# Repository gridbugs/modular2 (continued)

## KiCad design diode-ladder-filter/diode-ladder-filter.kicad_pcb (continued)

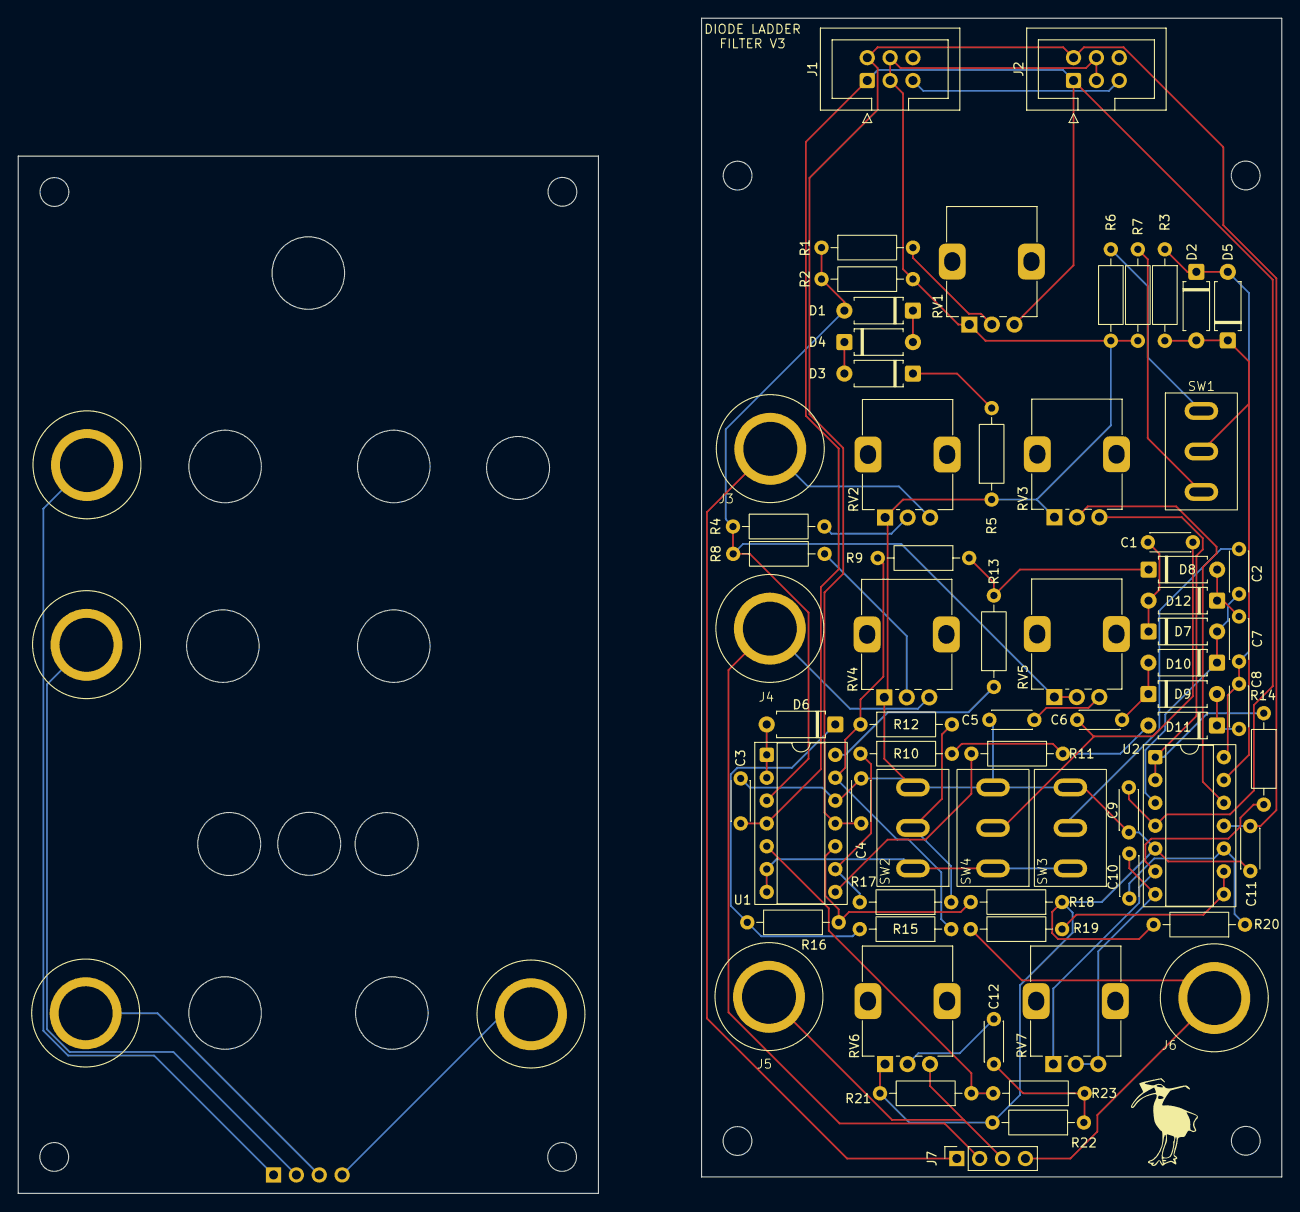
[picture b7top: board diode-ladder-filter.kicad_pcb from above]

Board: 2 copper layers, 64.5 x 128.8 mm, 80 parts (1 on the bottom side), 51 nets.

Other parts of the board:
H1, H2, H3, H4, H5, H6, H7, H8: MountingHole_3.2mm_M3

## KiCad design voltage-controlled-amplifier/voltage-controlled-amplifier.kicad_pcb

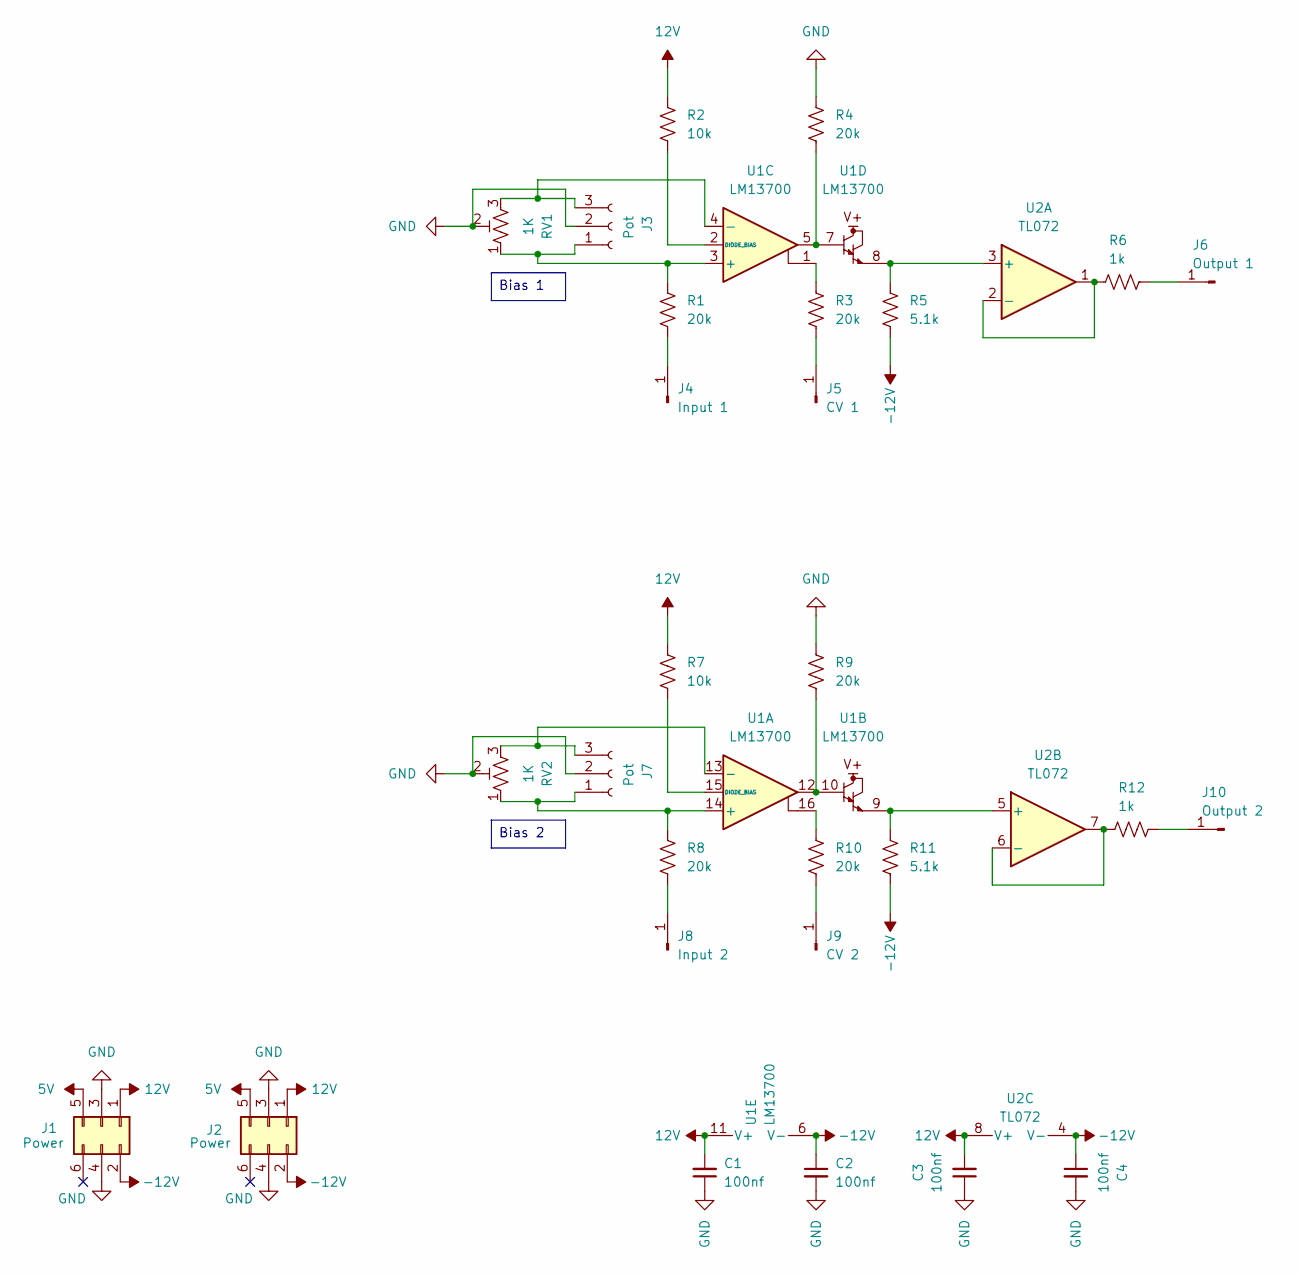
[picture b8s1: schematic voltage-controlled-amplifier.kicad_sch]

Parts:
C1, C2, C3, C4: 100nf; C_Disc_D4.3mm_W1.9mm_P5.00mm
J1, J2: Power; IDC-Header_2x03_P2.54mm_Vertical
J3, J7: Pot; pot
J4: Input 1; banana-jack
J5: CV 1; banana-jack
J6: Output 1; banana-jack
J8: Input 2; banana-jack
J9: CV 2; banana-jack
J10: Output 2; banana-jack
R1, R3, R4, R8, R9, R10: 20k; R_Axial_DIN0207_L6.3mm_D2.5mm_P10.16mm_Horizontal
R2, R7: 10k; R_Axial_DIN0207_L6.3mm_D2.5mm_P10.16mm_Horizontal
R5, R11: 5.1k; R_Axial_DIN0207_L6.3mm_D2.5mm_P10.16mm_Horizontal
R6, R12: 1k; R_Axial_DIN0207_L6.3mm_D2.5mm_P10.16mm_Horizontal
RV1, RV2: 1K; pot-socket
U1: LM13700; DIP-16_W7.62mm_Socket
U2: TL072; DIP-8_W7.62mm_Socket

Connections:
5V: J1.5, J2.5
12V: C1.2, C3.2, J1.1, J2.1, R2.1, R7.1, U1.11 (V+), U2.8 (V+)
-12V: C2.1, C4.1, J1.2, J2.2, R5.2, R11.2, U1.6 (V-), U2.4 (V-)
GND: C1.1, C2.2, C3.1, C4.2, J1.3, J1.4, J2.3, J2.4, J3.2, J7.2, R4.1, R9.1, RV1.2, RV2.2
unnamed: J3.1, R1.1, RV1.1, U1.3 (+)
unnamed: J3.3, RV1.3, U1.4 (-)
unnamed: J4.1, R1.2
unnamed: J5.1, R3.2
unnamed: J6.1, R6.2
unnamed: J7.1, R8.1, RV2.1, U1.14 (+)
unnamed: J7.3, RV2.3, U1.13 (-)
unnamed: J8.1, R8.2
unnamed: J9.1, R10.2
unnamed: J10.1, R12.2
unnamed: R3.1, U1.1
unnamed: R4.2, U1.5, U1.7
unnamed: R9.2, U1.10, U1.12
unnamed: R10.1, U1.16
unnamed: R7.2, U1.15 (DIODE_BIAS)
unnamed: R2.2, U1.2 (DIODE_BIAS)
unnamed: R5.1, U1.8, U2.3 (+)
unnamed: R6.1, U2.1, U2.2 (-)
unnamed: R11.1, U1.9, U2.5 (+)
unnamed: R12.1, U2.6 (-), U2.7

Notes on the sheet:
Bias 2
Bias 1

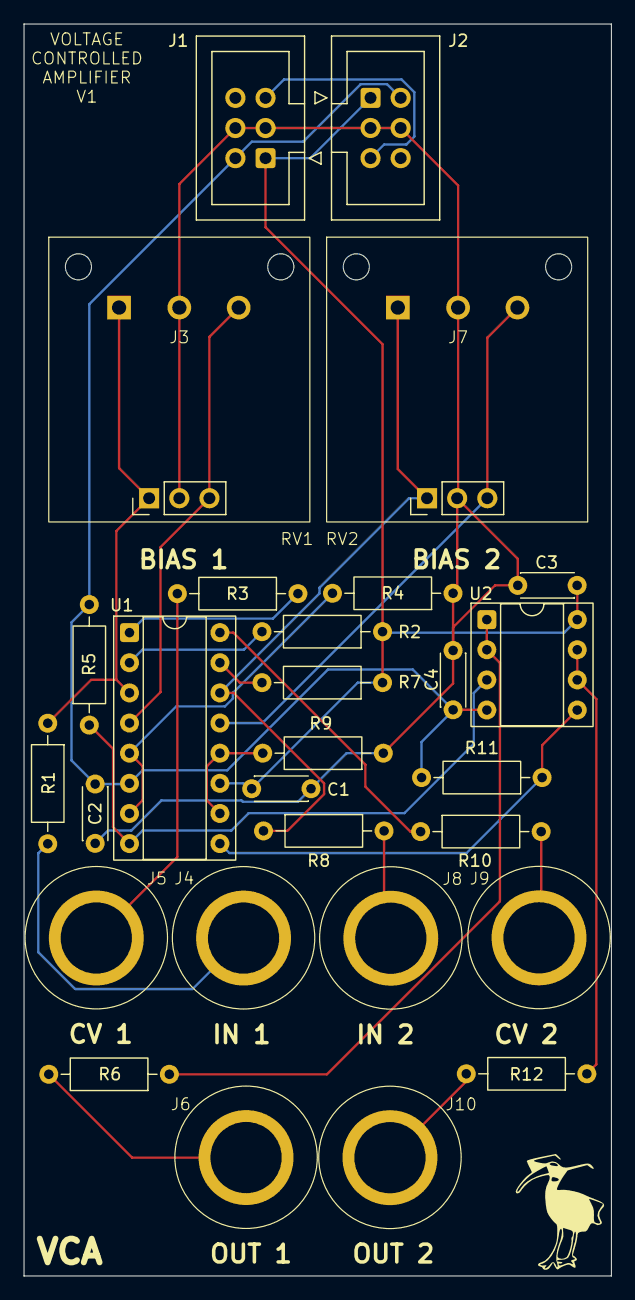
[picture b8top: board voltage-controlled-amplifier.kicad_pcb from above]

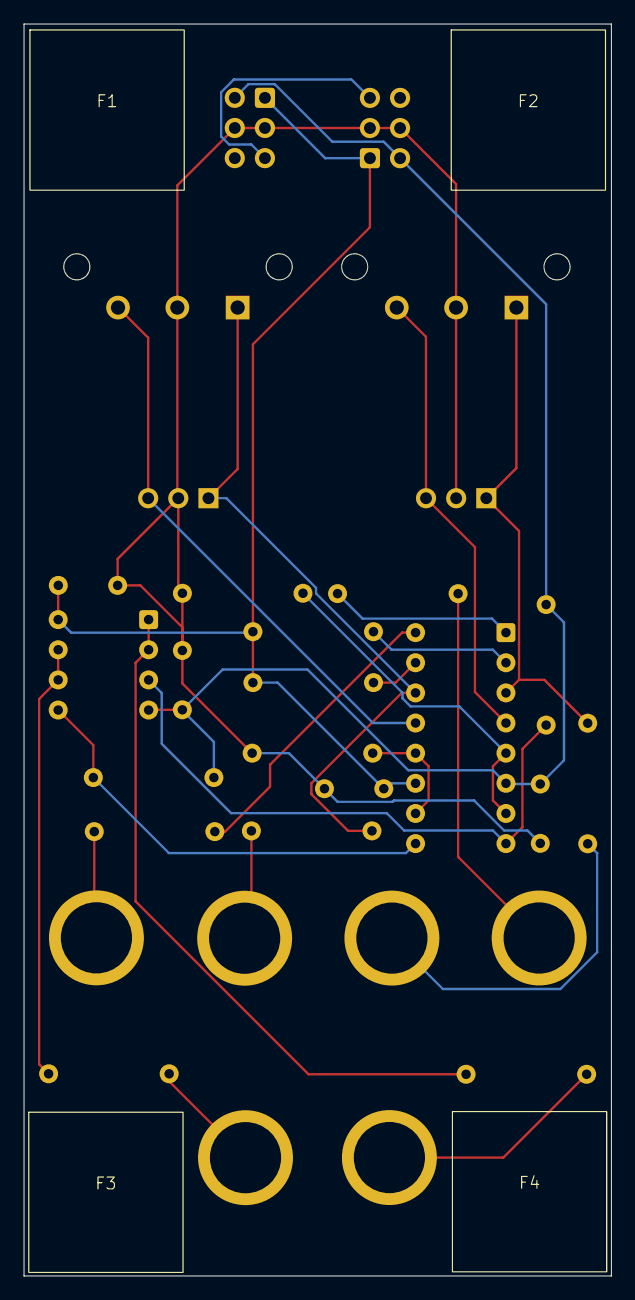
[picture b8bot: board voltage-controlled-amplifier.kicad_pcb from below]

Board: 2 copper layers, 49.5 x 105.5 mm, 34 parts (4 on the bottom side), 24 nets.

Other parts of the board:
F1, F2, F3, F4: foot

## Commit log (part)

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2025-11-22 Pot socket
2025-11-22 Docs, license
2025-11-23 Freecad design for pot socket
2025-11-25 Update pot socket model
2025-11-25 Update pcb outputs
2025-11-25 Remove redundant pcb stl
2025-12-03 Update pot socket
2025-12-03 Tidy pot socket design
2025-12-03 Update pot socket stl files
2025-12-03 Add padding to bottom of pot socket
2025-12-03 Update pot socket pcb
2025-12-04 Power supply
2025-12-04 First pass of power supply
2025-12-11 Add oscillator
2025-12-25 Update power supply
2025-12-25 Fix L812 orientation in power supply
2025-12-26 Redesign oscillator
2025-12-27 V2 of oscillator
2025-12-27 Notes
2025-12-27 Update oscillator
2025-12-27 Add mixer and power expander
2025-12-27 Add cv mixer
2025-12-28 Low-pass filter
2025-12-28 Add label to low-pass filter
2025-12-28 Envelope generator
2025-12-28 Add label to envelope generator
2026-01-01 Allow alternative heatsink on power supply
2026-01-04 Add vca
2026-01-05 Buffer output of vca
2026-01-09 More space for backup pot
2026-01-09 Envelope generator fixes
2026-01-09 More envelope generator fixes
2026-01-10 Various improvements
2026-01-11 Update low-pass filter
2026-01-15 Fix issues with audio mixer
2026-01-15 Various fixes
2026-01-20 Add attenuverter
2026-01-20 Clean up attenuverter
2026-01-20 Add attenuverter pdf
2026-01-20 Pattern sequencer
2026-01-20 Pdf of sequencer
2026-02-08 Fix attenuverter
2026-02-08 Update gerbers
2026-02-08 Vca fixes
2026-02-15 Arduino code for pattern sequencer
2026-02-16 Fixes
2026-02-23 Delay to allow debouncing caps to charge
2026-02-23 More pattern sequencer fixes
2026-02-23 Iterate on pattern sequencer firmware
2026-03-20 Update sequencer code
2026-03-22 Update pattern sequencer
2026-05-02 Progress on diode ladder
2026-05-03 Update diode ladder
2026-05-11 Update some modules
2026-05-15 Start fixing issues with diode ladder
2026-05-15 Diode ladder fixes and relayout
2026-05-18 Start of note sequencer
2026-05-18 Add ear protector
2026-05-18 Remove ear protector
2026-05-18 Start gate sequencer
2026-05-18 Progress gate sequencer
2026-05-19 Update note sequencer
2026-05-21 Renumber some components
2026-05-21 Revert "Renumber some components"
    This reverts commit 4c9a93e4336de2276d9b49e02718b6a92f997a6a.
2026-05-21 More fixes
2026-05-21 Fix issue with extra button
2026-05-21 Check in fabrication outputs
2026-05-23 Fix bug where cv mixer output was flipped
2026-05-23 Tweak cv mixer text
2026-05-23 More cv mixer updates
2026-05-23 Fix inverted output in audio mixer
2026-05-27 Start arduino delay design
2026-05-27 Arduino delay progress
2026-05-27 Complete arduino delay
2026-05-28 Update audio mixer to new format
2026-05-28 Fix some warnings
2026-06-03 Starting point for note sequencer firmware
2026-06-03 Fix pwm pin controlling screen brightness
2026-06-04 Key matrix
2026-06-04 Show current note on the screen
2026-06-05 Start firmware for gate sequencer
2026-06-05 Multilayer cv-mixer
2026-06-06 Update some designs
2026-06-07 Gate sequencer fixes
2026-06-07 Update gate sequencer
2026-06-07 Update diode ladder filter pdf
2026-06-09 Start on pattern sequencer 2 firmware
2026-06-11 Gate sequencer external clock
2026-06-12 Remove bitbanged uart
    Turns out the problem with uart on some arduinos isn't that the
    uart<->usb is broken, but that some (fake) arduinos appear to be
    effectively clocked 4x slower than expected, and this manifests in
    the speed of the cpu clock (programs run 4x slower) and devices like the
    uart.
2026-06-12 Update pattern sequencer schematic
2026-06-13 Pattern sequencer progress
2026-06-13 Basic pattern programming
2026-06-13 Programming mode for pattern sequencer
2026-06-14 Gate sequencer firmware
2026-06-17 Account for faster arduinos in note sequencer
2026-06-20 Refactor to share code between note seq arduinos
2026-06-20 Start on note sequencer ui
2026-06-20 Command framework for note sequencer
2026-06-21 Note sequencer programming interface
2026-06-21 Remove generated code
2026-06-21 Portable ctz
2026-06-21 Fix baud in doc
2026-06-21 More portable generate_tags.sh script
2026-06-21 Fix ctz
2026-06-24 Update pdf for oscillator
